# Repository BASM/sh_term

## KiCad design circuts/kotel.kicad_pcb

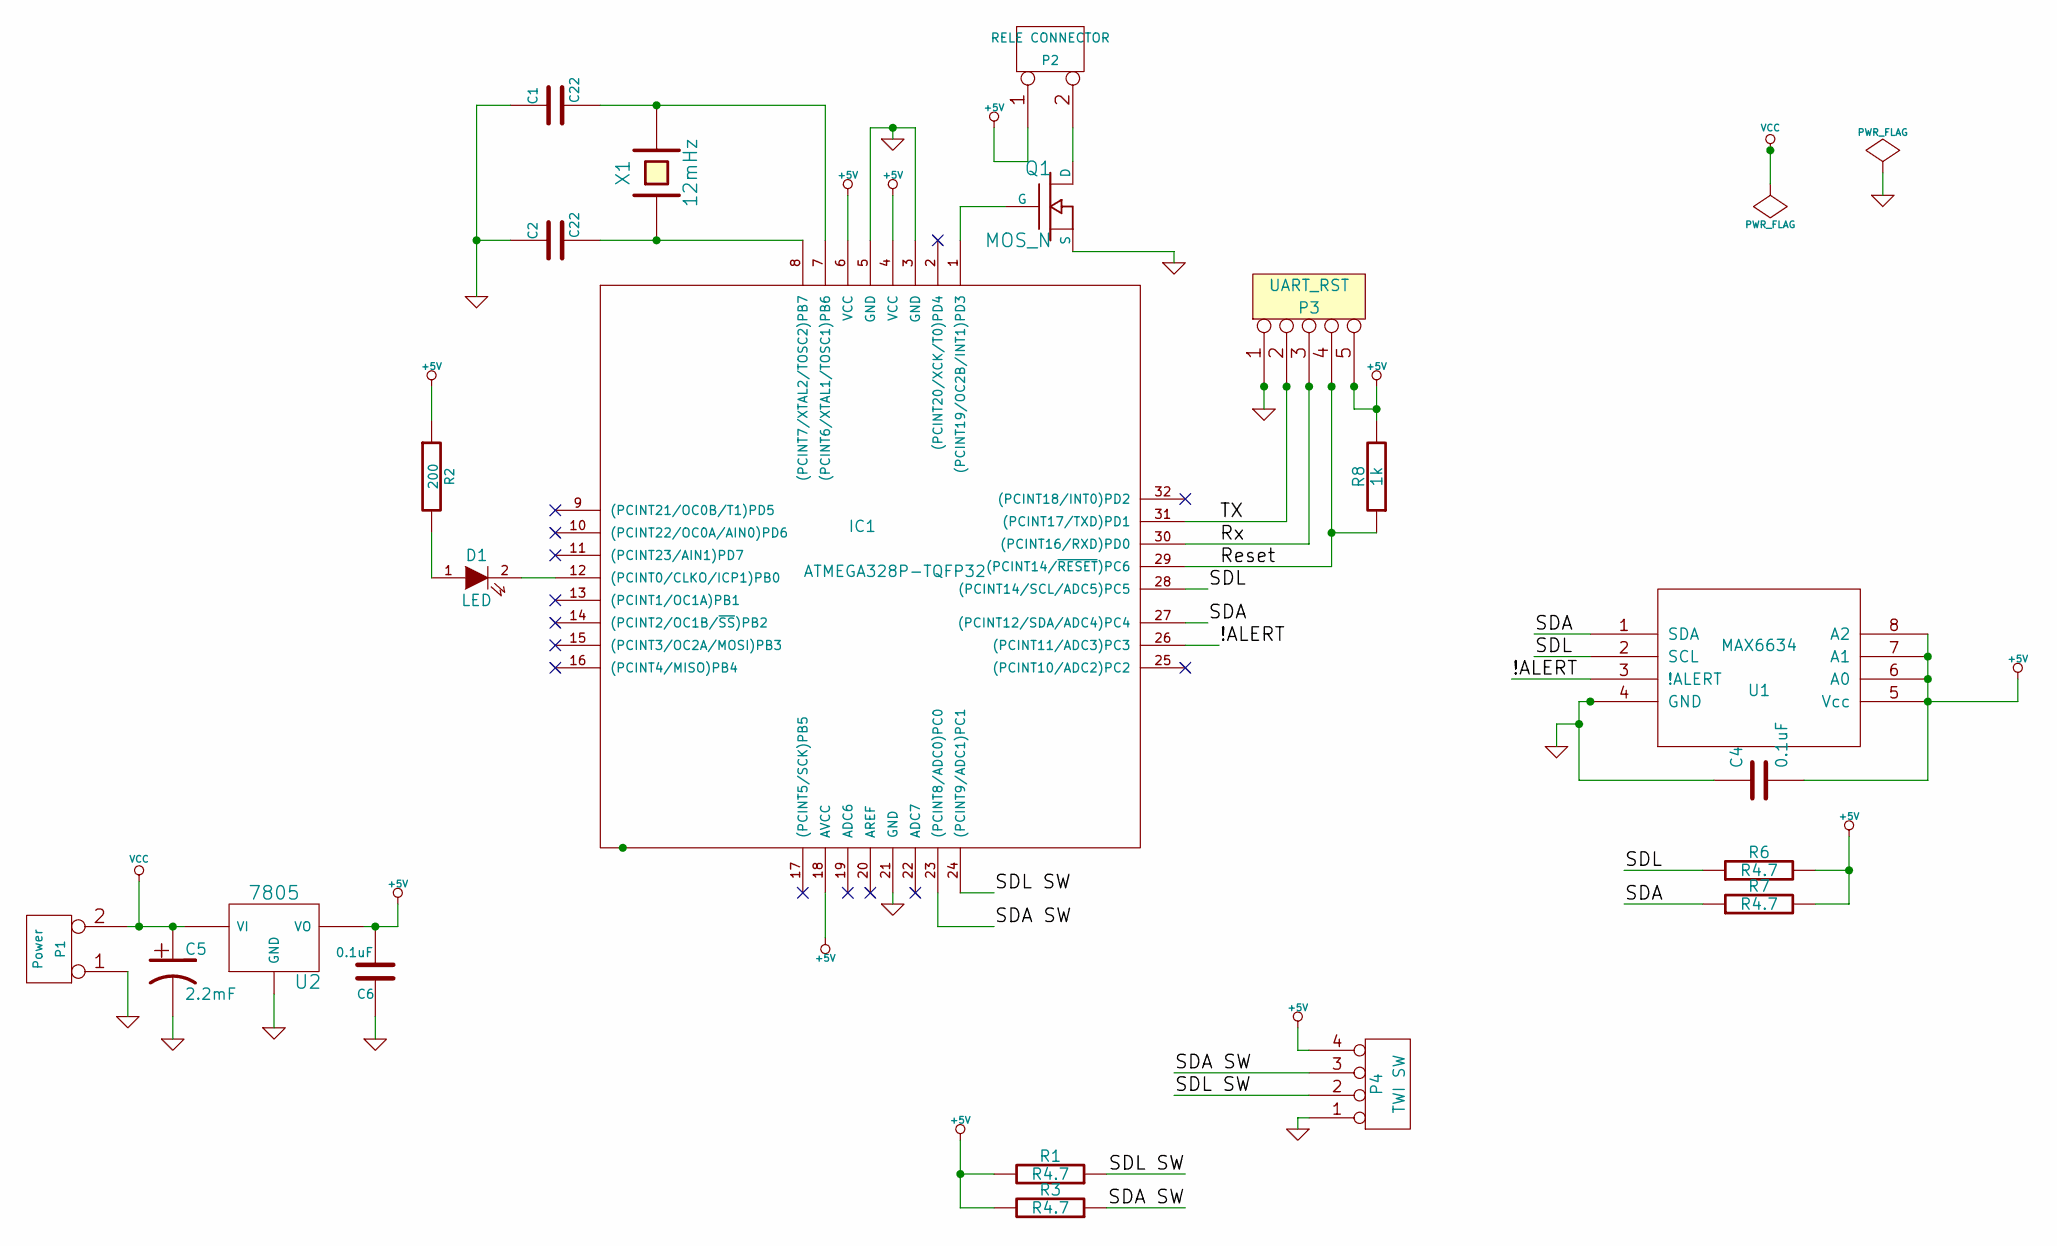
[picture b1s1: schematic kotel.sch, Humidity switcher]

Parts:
C1, C2: C22
C4: 0.1uF
C5: 2.2mF
C6: 0.1uF
D1: LED
IC1: ATMEGA328P-TQFP32; TQFP32
P1: Power
P2: RELE CONNECTOR
P3: UART_RST
P4: TWI SW
Q1: MOS_N
R1, R3, R6, R7: R4.7
R2: 200
R8: 1k
U1: MAX6634; MODULE
U2: 7805
X1: 12mHz

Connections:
+5V: C4.2, C6.2, IC1.4 (VCC), IC1.6 (VCC), IC1.18 (AVCC), P2.1, P3.5, P4.4, R1.2, R2.1, R3.2, R6.2, R7.2, R8.2, U1.5 (Vcc), U1.6 (A0), U1.7 (A1), U1.8 (A2), U2.VO
/!ALERT: IC1.26 ((PCINT11/ADC3)PC3), U1.3 (!ALERT)
/Reset: IC1.29 ((PCINT14/~RESET~)PC6), P3.4, R8.1
/Rx: IC1.30 ((PCINT16/RXD)PD0), P3.3
/SDA: IC1.27 ((PCINT12/SDA/ADC4)PC4), R7.1, U1.1 (SDA)
/SDA SW: IC1.24 ((PCINT9/ADC1)PC1), P4.2, R1.1
/SDL: IC1.28 ((PCINT14/SCL/ADC5)PC5), R6.1, U1.2 (SCL)
/SDL SW: IC1.23 ((PCINT8/ADC0)PC0), P4.3, R3.1
/TX: IC1.31 ((PCINT17/TXD)PD1), P3.2
GND: C1.1, C2.1, C4.1, C5.2, C6.1, IC1.3 (GND), IC1.5 (GND), IC1.21 (GND), P1.1, P3.1, P4.1, Q1.S, U1.4 (GND), U2.GND
unnamed: D1.1 (A), R2.2
unnamed: P2.2 (PM), Q1.D
unnamed: D1.2 (K), IC1.12 ((PCINT0/CLKO/ICP1)PB0)
unnamed: C1.2, IC1.7 ((PCINT6/XTAL1/TOSC1)PB6), X1.2
unnamed: C2.2, IC1.8 ((PCINT7/XTAL2/TOSC2)PB7), X1.1
unnamed: IC1.1 ((PCINT19/OC2B/INT1)PD3), Q1.G
VCC: C5.1, P1.2 (PM), U2.VI

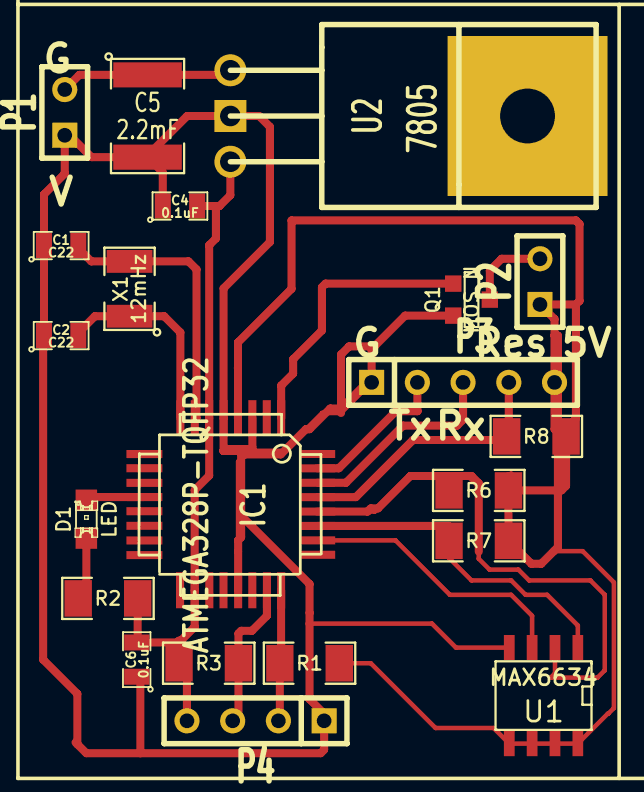
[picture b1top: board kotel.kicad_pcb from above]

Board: 2 copper layers, 21 parts (0 on the bottom side), 17 nets.

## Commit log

2013-09-29 Fixed cicruts
2013-09-29 Added skeleton for termNG program.
2013-09-29 Added gitmodules.
2013-10-06 Building from makefile projects.
2013-10-06 Fixed software SDL/SCL.
2013-10-06 Fixed name SDL to SCL.
2013-10-06 Libtwi renamed to libstwi
2013-10-06 Worked variant this libstwi (Lib Software TWI)
2013-10-09 Software twi configuration moved to support file.
2013-10-09 Collecting data from thermometers
2013-10-09 Fixed gitmodules.
2013-10-11 Moved makefiles to ../makefiles
2013-10-13 Prerelease version (minimal functional)
2013-10-13 Added PC skeleton.
2014-06-24 Added libavr submodule
